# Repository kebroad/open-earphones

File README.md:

# Open Earphones

Open Source Modular Earphones that will last a lifetime if you build/fix them yourself.

After spending years buying earphones that would either break or have the battery die, I wanted to build my own pair from scratch in order to be able to repair or replace parts on it easily. Based off of Microchip's IS2083 chip and module, I prototyped custom circuit boards along with 3D printing the case in ABS and the ear-bud tips in flexible TPU.

CAD Files and  PCB files are available in this repo. BOM and a tutorial on how to put assemble them is coming soon.

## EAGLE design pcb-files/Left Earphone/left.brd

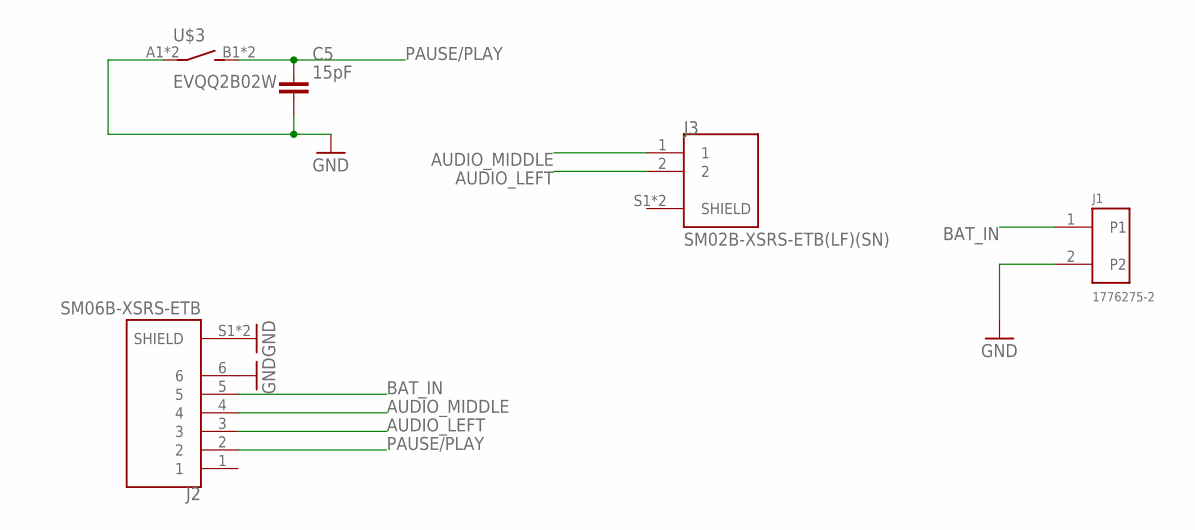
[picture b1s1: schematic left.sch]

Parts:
C5: 15pF; CAPC2012X110
J1: 1776275-2; TE_1776275-2
J2: SM06B-XSRS-ETB; JST_SM06B-XSRS-ETB
J3: SM02B-XSRS-ETB(LF)(SN); JST_SM02B-XSRS-ETB(LF)(SN)
U$3: EVQQ2B02W

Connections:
AUDIO_LEFT: J2.3, J3.2
AUDIO_MIDDLE: J2.4, J3.1
BAT_IN: J1.1, J2.5
GND: C5.2, J1.2, J2.6, J2.S1 (SHIELD), J2.S2 (SHIELD), U$3.A1, U$3.A2
PAUSE/PLAY: C5.1, J2.2, U$3.B1 (S), U$3.B2 (S)

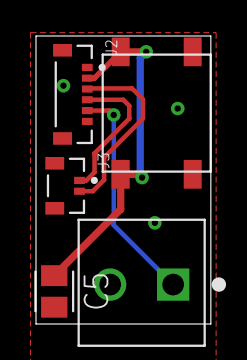
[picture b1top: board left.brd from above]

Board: 2 copper layers, 9.7 x 16.0 mm, 5 parts (0 on the bottom side), 5 nets.

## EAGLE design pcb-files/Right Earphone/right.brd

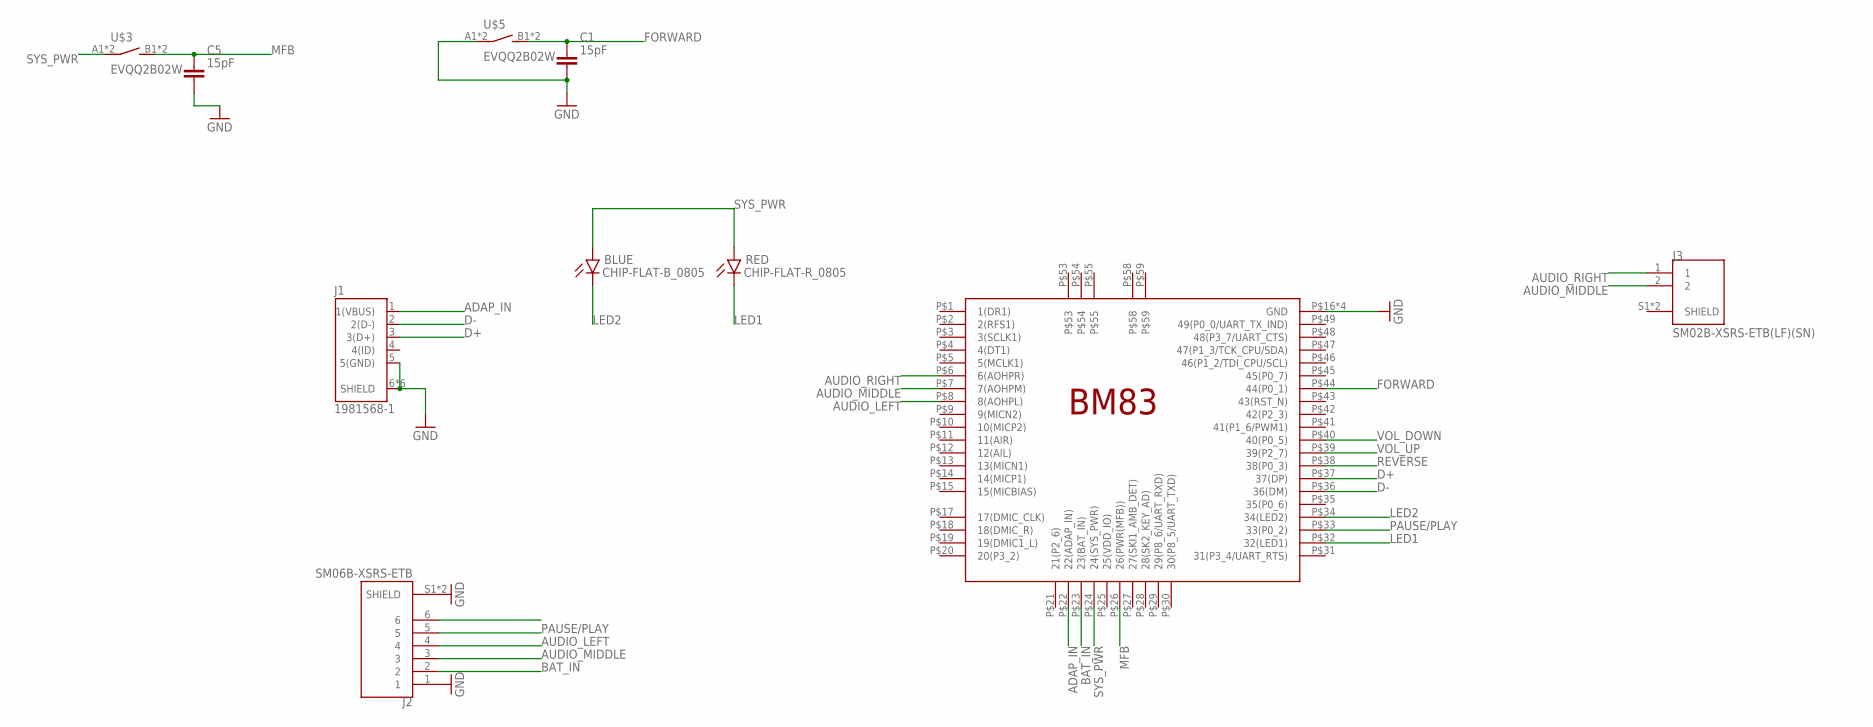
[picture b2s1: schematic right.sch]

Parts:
BLUE: CHIP-FLAT-B_0805; LEDC2012X110N
C1, C5: 15pF; CAPC2012X110
J1: 1981568-1; TE_1981568-1
J2: SM06B-XSRS-ETB; JST_SM06B-XSRS-ETB
J3: SM02B-XSRS-ETB(LF)(SN); JST_SM02B-XSRS-ETB(LF)(SN)
RED: CHIP-FLAT-R_0805; LEDC2012X110N
U$1: BM83
U$3, U$5: EVQQ2B02W

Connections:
ADAP_IN: J1.1 (1(VBUS)), U$1.P$22 (22(ADAP_IN))
AUDIO_LEFT: J2.4, U$1.P$8 (8(AOHPL))
AUDIO_MIDDLE: J2.3, J3.2, U$1.P$7 (7(AOHPM))
AUDIO_RIGHT: J3.1, U$1.P$6 (6(AOHPR))
BAT_IN: J2.2, U$1.P$23 (23(BAT_IN))
D+: J1.3 (3(D+)), U$1.P$37 (37(DP))
D-: J1.2 (2(D-)), U$1.P$36 (36(DM))
FORWARD: C1.1, U$1.P$44 (44(P0_1)), U$5.B1 (S), U$5.B2 (S)
GND: C1.2, C5.2, J1.5 (5(GND)), J1.6 (SHIELD), J1.7 (SHIELD), J1.8 (SHIELD), J1.9 (SHIELD), J1.10 (SHIELD), J1.11 (SHIELD), J2.1, J2.S1 (SHIELD), J2.S2 (SHIELD), U$1.P$16 (GND), U$1.P$50 (GND), U$1.P$56 (GND), U$1.P$57 (GND), U$5.A1, U$5.A2
LED1: RED.C, U$1.P$32 (32(LED1))
LED2: BLUE.C, U$1.P$34 (34(LED2))
MFB: C5.1, U$1.P$26 (26(PWR(MFB))), U$3.B1 (S), U$3.B2 (S)
PAUSE/PLAY: J2.5, U$1.P$33 (33(P0_2))
REVERSE: U$1.P$38 (38(P0_3))
SYS_PWR: BLUE.A, RED.A, U$1.P$24 (24(SYS_PWR)), U$3.A1, U$3.A2
VOL_DOWN: U$1.P$40 (40(P0_5))
VOL_UP: U$1.P$39 (39(P2_7))

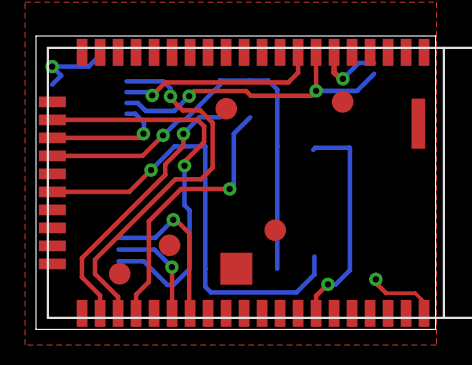
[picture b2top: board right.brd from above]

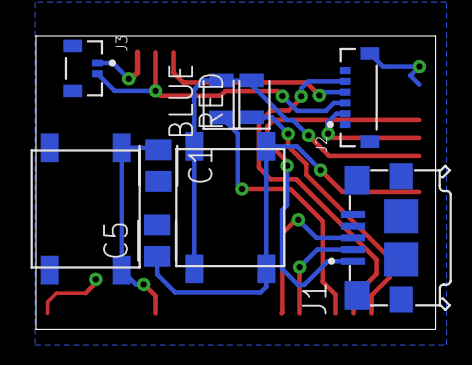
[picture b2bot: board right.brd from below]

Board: 2 copper layers, 22.2 x 16.3 mm, 10 parts (9 on the bottom side), 14 nets.

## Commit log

2021-01-28 added software binaries for BM83
